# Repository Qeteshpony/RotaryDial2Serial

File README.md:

# RotaryDial2Serial

[Hardware Documentation](https://qeteshpony.github.io/RotaryDial2Serial)

This little board allows using the rotary dial of an old phone as an input for modern electronics by translating the signals into serial data.

You need to find the right contacts from the rotary dial mechanism and the phone hook (if you want to use it) and connect them to this board. The board will work with 3.3V or 5V and uses very little power so it can be driven directly from a Raspberry Pi or even an ESP or similar microcontroller.

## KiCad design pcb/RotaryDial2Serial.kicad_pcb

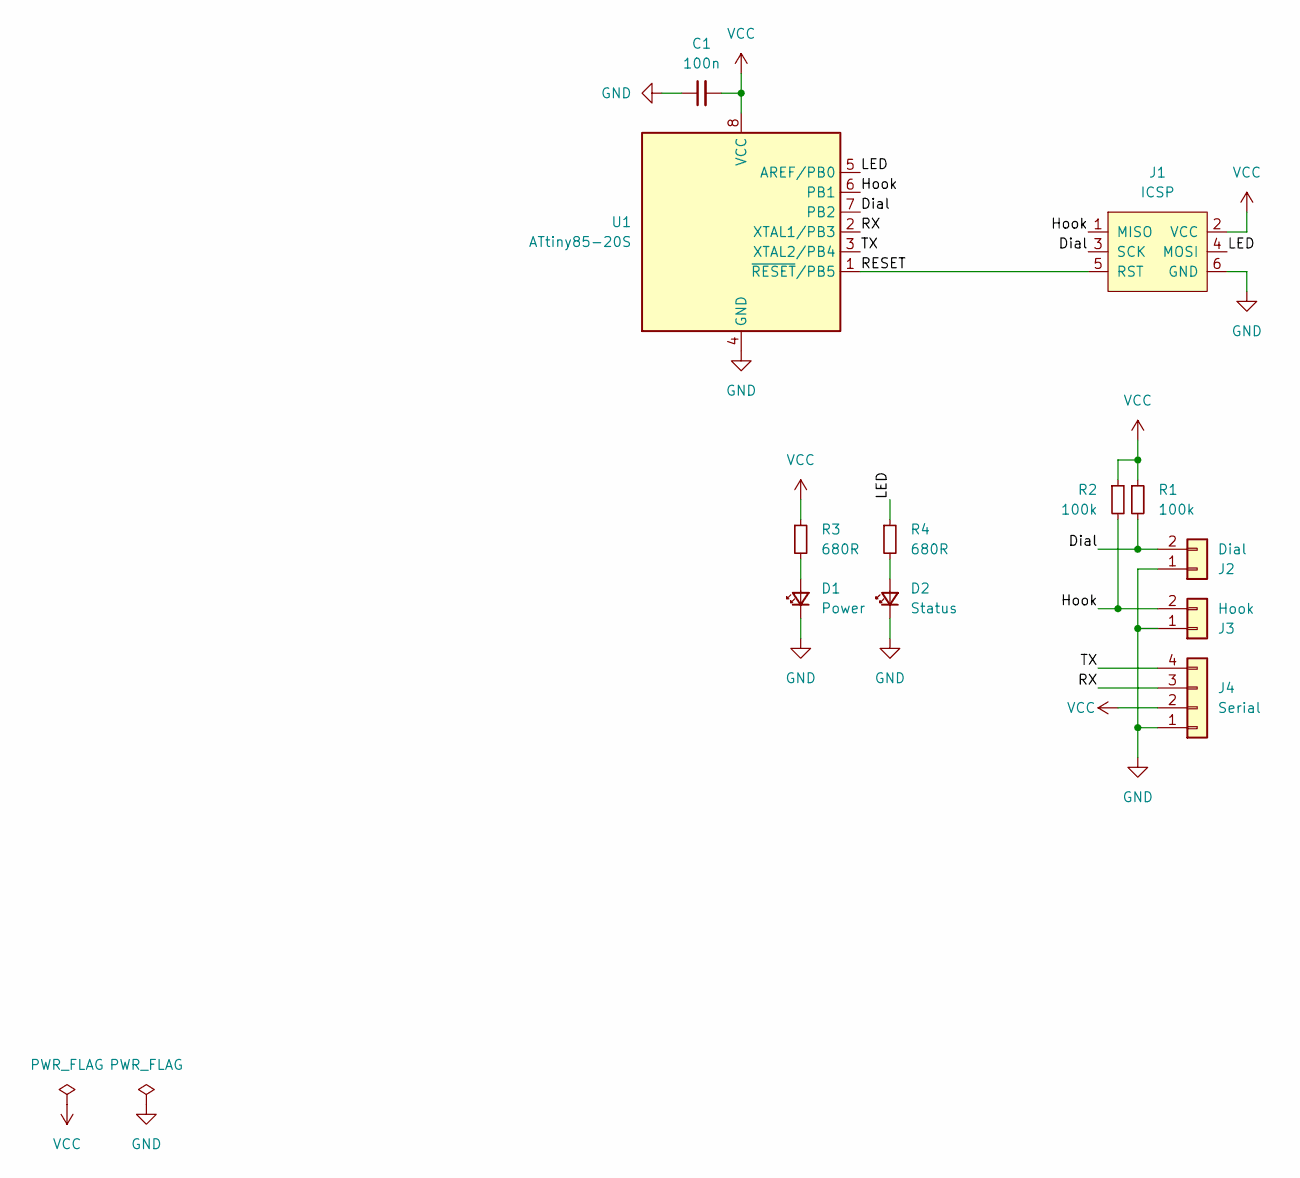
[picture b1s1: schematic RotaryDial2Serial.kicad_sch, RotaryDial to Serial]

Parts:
C1: 100n; C_0603_1608Metric_Pad1.08x0.95mm_HandSolder
D1: Power; LED_0603_1608Metric_Pad1.05x0.95mm_HandSolder
D2: Status; LED_0603_1608Metric_Pad1.05x0.95mm_HandSolder
J1: ICSP; PinHeader_2x03_P2.54mm_Vertical
J2: Dial; JST_PH_B2B-PH-K_1x02_P2.00mm_Vertical
J3: Hook; JST_PH_B2B-PH-K_1x02_P2.00mm_Vertical
J4: Serial; JST_PH_B4B-PH-K_1x04_P2.00mm_Vertical
R1, R2: 100k; R_0603_1608Metric_Pad0.98x0.95mm_HandSolder
R3, R4: 680R; R_0603_1608Metric_Pad0.98x0.95mm_HandSolder
U1: ATtiny85-20S; SOIC-8W_5.3x5.3mm_P1.27mm

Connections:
/Dial: J1.3 (SCK), J2.2, R1.2, U1.7 (PB2)
/Hook: J1.1 (MISO), J3.2, R2.2, U1.6 (PB1)
/LED: J1.4 (MOSI), R4.1, U1.5 (AREF/PB0)
/RESET: J1.5 (RST), U1.1 (~RESET/PB5)
/RX: J4.3, U1.2 (XTAL1/PB3)
/TX: J4.4, U1.3 (XTAL2/PB4)
GND: C1.1, D1.1 (K), D2.1 (K), J1.6 (GND), J2.1, J3.1, J4.1, U1.4 (GND)
unnamed: D1.2 (A), R3.2
unnamed: D2.2 (A), R4.2
VCC: C1.2, J1.2 (VCC), J4.2, R1.1, R2.1, R3.1, U1.8 (VCC)

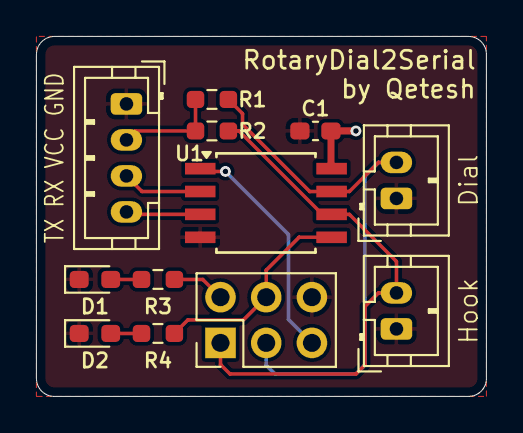
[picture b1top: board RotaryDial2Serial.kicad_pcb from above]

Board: 2 copper layers, 25.0 x 20.0 mm, 12 parts (0 on the bottom side), 10 nets.

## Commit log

2024-07-23 feat: initial commit
2024-07-23 chore(main): release 1.0.0
2024-07-23 docs: fix image link
2024-07-23 docs: fix typo
2024-08-01 fix: improve debouncing for the hook switch
2024-08-01 fix: set LED pin to output
2024-08-01 fix: type of timer variables
2024-08-01 chore(main): release 1.0.1
2024-08-29 ci: remove dependency between jobs
2025-12-21 fix: replace interrupt with loop checks
    The interrupt didn't work as expected because the switches in the old rotary dialers swing too much so it got replaced. This now works 100% of the time
